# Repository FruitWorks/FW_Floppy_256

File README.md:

# Floppy256

A 256Kbit (32KB) I²C EEPROM shaped like a miniature 3.5" floppy disk.

Made by [FruitWorks](#).

## What it is

Floppy256 is a small I²C EEPROM module inspired by the classic 3.5" floppy disk and the familiar save icon.

The idea came from looking at generic EEPROM breakout boards and wondering why a memory module had to look like every other little PCB. I wanted to take something simple and useful and give it a bit of retro-computing personality.

It uses a 256Kbit EEPROM and provides a simple four-pin I²C interface for adding non-volatile storage to microcontroller projects.

## Specs

| | |
|---|---|
| EEPROM | ST M24256-DFMN6TP |
| Capacity | 256 Kbit / 32 KB |
| Interface | I²C |
| Default I²C Address | `0x50` |
| Address Pins | A0, A1, A2 strapped low |
| Page Size | 64 bytes |
| EEPROM Supply Voltage | 1.7V–5.5V |
| Pinout | SDA, SCL, VCC, GND |

The EEPROM address is determined by A0/A1/A2. In the current Floppy256 hardware design, these pins are tied low, giving a default address of `0x57`.

For a 3.3V microcontroller, power the module from 3.3V. For a 5V system, power it from 5V. The host MCU I²C logic level should match the module supply voltage.

Datasheet: [ST M24256-DF](https://www.st.com/en/memories/m24256-df.html)

## Pinout

| Pin | Function |
|---|---|
| SDA | I²C data |
| SCL | I²C clock |
| VCC | Power |
| GND | Ground |

## Wiring

```text
Floppy256       Microcontroller
-----------     --------------
VCC       ----> 3.3V or 5V*
GND       ----> GND
SDA       ----> I²C SDA
SCL       ----> I²C SCL
```

`*` Use a supply voltage appropriate for your MCU's I²C logic level.

The board includes the I²C pull-up resistors required for normal operation.

## Getting Started

### Arduino example

The following example writes a short message to address `0` and reads it back.

```cpp
#include <Wire.h>

#define EEPROM_ADDR 0x57

void writeEEPROM(uint16_t address, const char *text) {
  Wire.beginTransmission(EEPROM_ADDR);
  Wire.write(address >> 8);
  Wire.write(address & 0xFF);

  while (*text) {
    Wire.write(*text++);
  }

  Wire.endTransmission();
  delay(10);
}

void readEEPROM(uint16_t address, char *buffer, size_t length) {
  Wire.beginTransmission(EEPROM_ADDR);
  Wire.write(address >> 8);
  Wire.write(address & 0xFF);
  Wire.endTransmission(false);

  Wire.requestFrom(EEPROM_ADDR, (uint8_t)length);

  size_t i = 0;
  while (Wire.available() && i < length - 1) {
    buffer[i++] = Wire.read();
  }

  buffer[i] = '\0';
}

void setup() {
  Serial.begin(115200);
  Wire.begin();

  writeEEPROM(0, "Hello from Floppy256!");

  char data[32];
  readEEPROM(0, data, sizeof(data));

  Serial.println(data);
}

void loop() {
}
```

Serial Monitor output:

```text
Hello from Floppy256!
```
## Floppy256 in Action

Floppy256 works with a wide range of microcontrollers through the standard I²C interface.

Floppy256 connected to Raspberry Pi Pico

Floppy256 connected to STM32 Bluepill

Floppy256 connected to ESP32 Development Boards

## Open Source / Build Your Own

Floppy256 is an open hardware project.

If you build your own Floppy256, a credit or link back to FruitWorks is appreciated.

If you make improvements or create your own version, feel free to share them.

## Manufacturing

Floppy256 was designed in KiCad and is produced in very small batches.

The design uses standard PCB manufacturing and assembly processes and commonly available components.

## License

The hardware, software, documentation, and images in this repository are intended to remain open.

See the license files included in this repository for the applicable terms.

## Credits

Designed and built by **FruitWorks**.

Floppy256 is a small independent hardware project made in very small batches.

## Get One

Floppy256 is available from [Tindie](#).

Made for makers, retro-computing fans, and anyone who thinks a floppy-shaped EEPROM is a little more fun than a generic breakout board.

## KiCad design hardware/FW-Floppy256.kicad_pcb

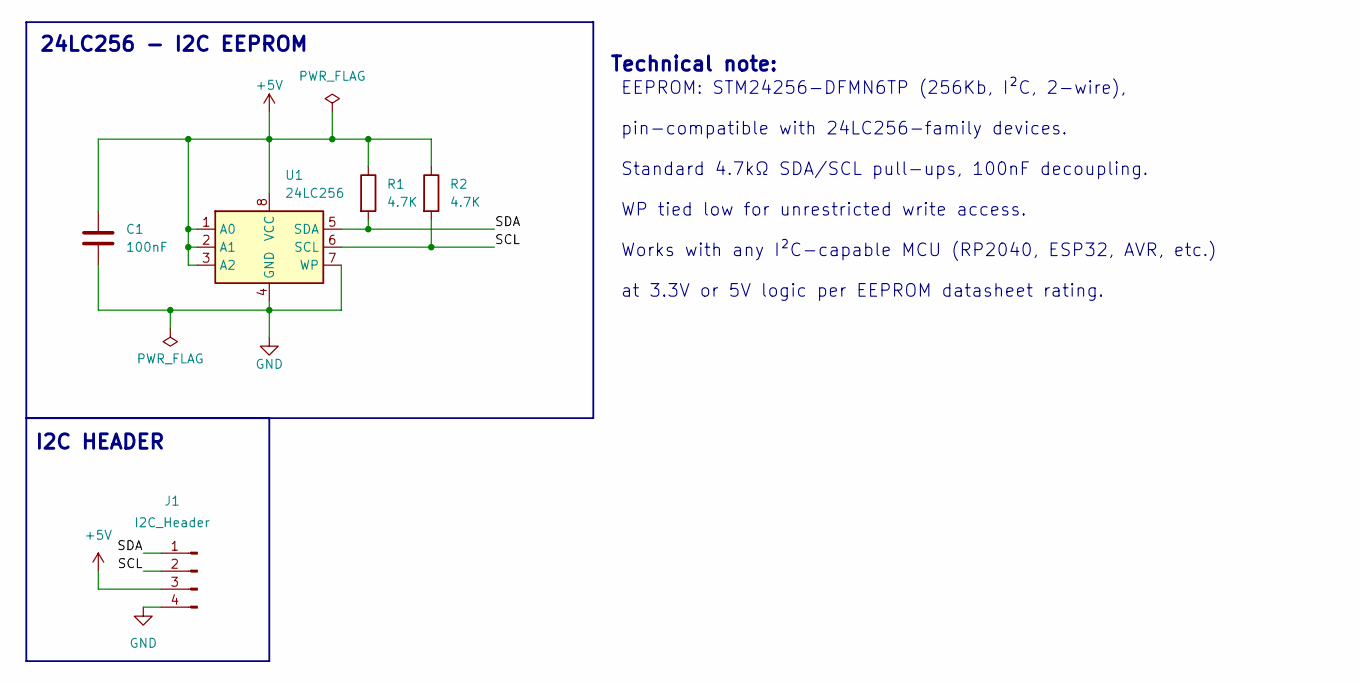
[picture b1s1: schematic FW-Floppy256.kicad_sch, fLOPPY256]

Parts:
C1: 100nF; C_0805_2012Metric_Pad1.18x1.45mm_HandSolder
J1: I2C_Header; PinHeader_1x04_P2.54mm_Vertical
R1, R2: 4.7K; R_0805_2012Metric_Pad1.20x1.40mm_HandSolder
U1: 24LC256; SOIC-8_3.9x4.9mm_P1.27mm

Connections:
+5V: C1.1, J1.3, R1.1, R2.1, U1.1 (A0), U1.2 (A1), U1.3 (A2), U1.8 (VCC)
/SCL: J1.2, R2.2, U1.6 (SCL)
/SDA: J1.1, R1.2, U1.5 (SDA)
GND: C1.2, J1.4, U1.4 (GND), U1.7 (WP)

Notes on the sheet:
EEPROM: STM24256-DFMN6TP (256Kb, I²C, 2-wire), pin-compatible with 24LC256-family devices. Standard 4.7kΩ SDA/SCL pull-ups, 100nF decoupling. WP tied low for unrestricted write access. Works with any I²C-capable MCU (RP2040, ESP32, AVR, etc.) at 3.3V or 5V logic per EEPROM datasheet rating.
24LC256 - I2C EEPROM
Technical note:
I2C HEADER

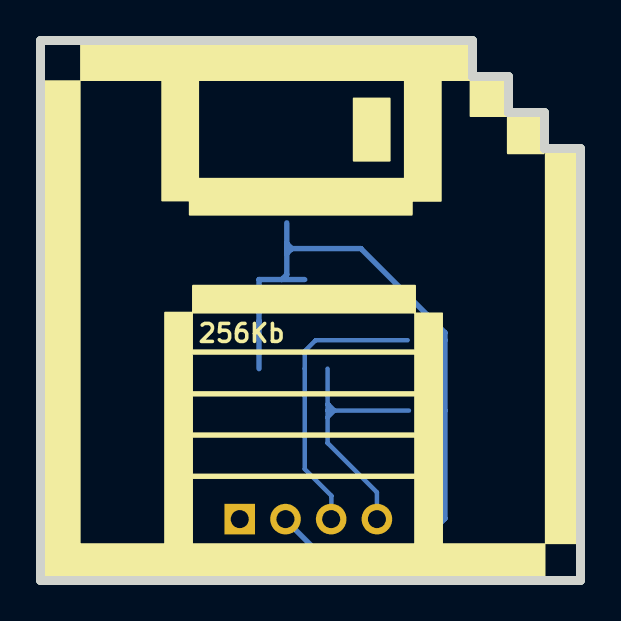
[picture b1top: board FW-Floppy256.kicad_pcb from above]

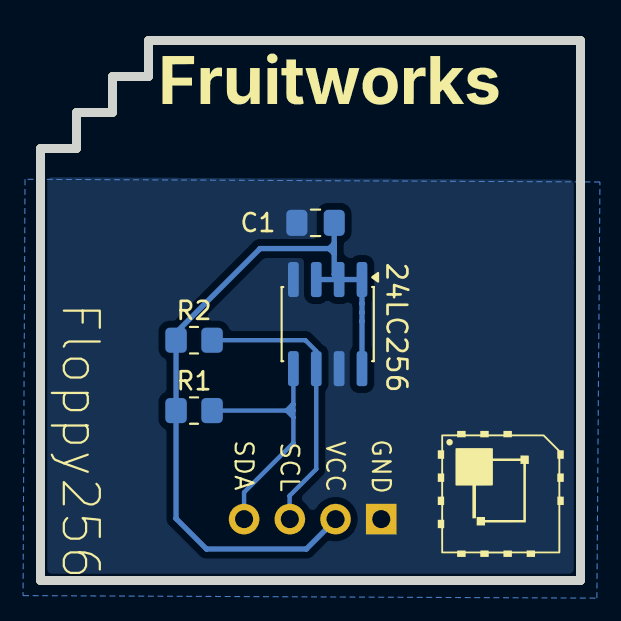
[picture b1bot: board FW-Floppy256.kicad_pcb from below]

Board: 2 copper layers, 30.0 x 30.0 mm, 5 parts (4 on the bottom side), 4 nets.
